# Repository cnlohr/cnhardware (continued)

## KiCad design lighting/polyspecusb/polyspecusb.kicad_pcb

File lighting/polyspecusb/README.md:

TODO:
1. Add resistor on ABC boards
2. Make D board (when more LEDs come)
3. Digitize the post-it notes.
4. Take pictures of the boards.
5. Classify radiance.
6. Fix flakeyness with 570funprog programmer

# Methodology

Test program:
```c
	SystemInit();
	Delay_Ms( 1800 );
	funGpioInitAll(); // Enable GPIOs
	GPIOC->CFGLR = 0x11111111;
	GPIOD->CFGLR = 0x44441144; // PD2..3 outputs
	while(1)
	{
		GPIOC->OUTDR = LEDMASK;
		GPIOD->OUTDR = (LEDMASK>>8)<<2;
		ADD_N_NOPS( 15 );
		GPIOC->OUTDR = 0x00;
		GPIOD->OUTDR = 0b0000;
		ADD_N_NOPS( 30 );  (or 300 for IR, etc.)
	}
```

Target wattage: ~1W (+/- 50%)

Settings on SpectraScan PR670:
ND1000 Filter, using 75mm 1:2.7
6ms integration time.
Focus on board

**Radiance values are approximate, and will vary by power, DO NOT USE FOR ABSOLUTE TERMS**

# LEDs

### 490-500 Ice Blue
Board A, top1, .66W (4.94V, 0.133A)
490-500, 3W Aixinde, "Ice Blue", 3W3535H490IB

### 450-460 Royal Blue
Board A, top2, .73W (4.94V, 0.149A)
450-460, 3W Aixinde, "Royal Blue", 3W3535XSJ450RB

### 520-530 Green
Board A, top3, .579W (4.95V, 0.116A)
520-530, 3W Aixinde, "Green" 3W3535XSJ520G / 3W3535XSJ5205?
1.57 W/sr/m^2, 516nm

### IR730
Board A, top4, LOW POWER, 2.27W (4.8V, 0.475A)
730nm, 3W Aixinde, "IR730" 3W3535Y730IR
3 W/sr/m^2, 730nm

### Deep Red 660
Board A, mid3, 1.341W (4.895V, 0.273A)
Unknown source (First batch)
7.55 W/sr/m^2, 662nm

### "Blue"
Board A, bottom3, 0.902W (4.931V, 0.182A)
Unknown source (very first batch)
4.18 W/sr/m^2, 462nm

### "Yellow"
Board A, mid2, 2.162W (4.829V, 0.447A)
YinYao Yellow 590-592 "3535XPE"
1.55 W/sr/m^2, 602nm

### 560-565 Green
Board A, bottom2, 1.211W (4.908V, .250A)
HF3534D120-3W-560-0745J9 560-565
1.2 W/sr/m^2, 552nm

### "Blue"
Board A, bottom1, .761W (4.946V, .152A)
3W3535BH470B (or is it 3W3535GH470B?) Blue Axinide 470-475
4.4 W/sr/m^2, 468nm

### "Golden"
Board A, mid1, LOW POWER 1.579W (4.879V, .372A)
3535XPE Yin Yao 1900k 3.0-3.2V Golden
1.56W/sr/m^2, SPREAD 622nm

## Board B

### 590-595 Yellow
Board B, top1, 1.38W (4.893V, 0.282A)
3W3535GH590Y
1.19W/sr/m^2 596nm

### "Red" 
Board B, top2, 1.72W (4.865V, 0.353A)
Unknown Red
8.72W/sr/m^2 634nm

### "Yellow"
Board B, top3, 1.40W (4.88V, 0.286A)
Yellow
1.47W/sr/m^2 598nm

### 590-595 Yellow 
Board B, top4, 1.37W (4.89V, .283A)
3W3535GH590Y Yellow 590-595nm Aixinde
1.33W/sr/m^2 596nm

### UV395
Board B, mid3, .722W (4.95V, .144A)
First Batch
3.46W/sr/m^2 398nm

### "440-445"
Board b, bottom3, .810W (4.94V, .161A)
First Batch
2.52 438

### "Golden"
Board B, mid2, LOW POWER 1.55W (4.875V, .312A)
First Batch
1.73 SPREAD 604

## "500-510"
Board b bottom2, 1.241W (4.91V, .258A)
First batch
3.2 498nm

## "460-470"
Board b, bottom1, .688W (4.95V, .140A)
First Batch
3.4 462nm

## 440-445 "Royal Blue"
Board b, mid1, .588W (4.95V, .136A)
First BAtch
3.86 438nm

## Blue "450-460"
Board c, top1, .709w (4.93V .147A)
2.62 W/sr/m^2 446nm

## Lake Blue "470-475"
Board c, top2, .617w (4.94V, .125A)
4.05 W/sr/m^2 468nm

## Ice Blue 490-495
Board c, top 3, .632W (4.94V, .127A)
2.5 W, 490nm

## 520-525
Board C, top 4, .574W (4.95V, .117A)
2.4 W, 514nm

## 545-550
Board C, mid 3, .658W (4.95V, .135A)
1.1W, 540nm

## 560-565
Board C, bottom3, LOW POWER, .8W (4.94V, .170A)
.617, 542nm

## 520-530
Board c, mid2, 1.004W (.493V, .260A)
3.92, 516nm

## 555-560
Board C, bottom2, 1.272W (4.897V, .266A)
2.31, 544nm

## 550-555
Board C, Bottom1, .707W (4.947V, .144A)
1.3, 544nm

## 530-535
Board C, mid1, .677 (4.949, .137A)
1.96, 526nm

## 560-570
D, top1  .678w (4.949V, .138A)
9.17, 552nm

## 580-585
D, top2 .648 (4.954V, .131A)
"Alt new order"
2.37, 612nm

## 575 "Cyan Yellow"
D, top3, .707 (4.95, .140A)
.923, 552nm

## 580-585 ZQQMU
D, top4, 1.203 (4.911, .241A)
.42, 584nm

##590-595
D, mid3, 1.291 (4.906, .253)
2.03, 598nm

##Red 620
D, bottom3, LOW POWER 1.71W (4.855, .367)
New Batch Red
3.93, 628nm

##585-590
D, middle2, 1.715 (4.856, .354A)
From group of oranges
1.38, 596nm

##620-630
D, bottom2, 2.52 (4.802, .521A)
Unknown but first group, probably oranges.
11.5W, 634nm

##600-605
D, bottom1, 1.908W (4.851V, .392A)
From first group of oranges
3.75, 616nm

##570-580
D, mid1, 1.11W (4.922, .229A)
I think yellows or oranges.
1.22, 558nm

## 660 deep red
E, top1, 1.178W (4.914, .239A)
8.17, 656nm

## 700nm 
E, top2, 1.756W (4.870, .359A)
Single Item (New)
9.31, 704nm

## 480-485
E, top3, .722W (4.951, .145A)
FROM NEW BATCH!
3.57, 484nm

## 940nm
E, top4, 3.11W (4.755, .653)
From new batch, single item
Deep glow. Does not effectively measure.

## 365-370
E, mid3, .811W (4.948, .167)
From new batch (I think, maybe?)
Cannot measure, has pale indigo glow.

## 850nm
E mid2, 3.46W (4.725, .731A)
No ND1000 filter, 100W/sr/m^2, off chart 780nm

## ??? Found on floor
E, bottom2, 1.08W (4.964, .223A)
3.8W, 514nm

## 1050nm
E bottom1, LOW POWER 3.064W (4.746, .647) (was 9W at low power)
What is this monstrosity?
I liked it because even while it's burning my corneas off, it has this really deep ethereal red glow.

## IR730
E mid1, LOW POWER 2.523W (4.800, .527)
3.52, 734nm

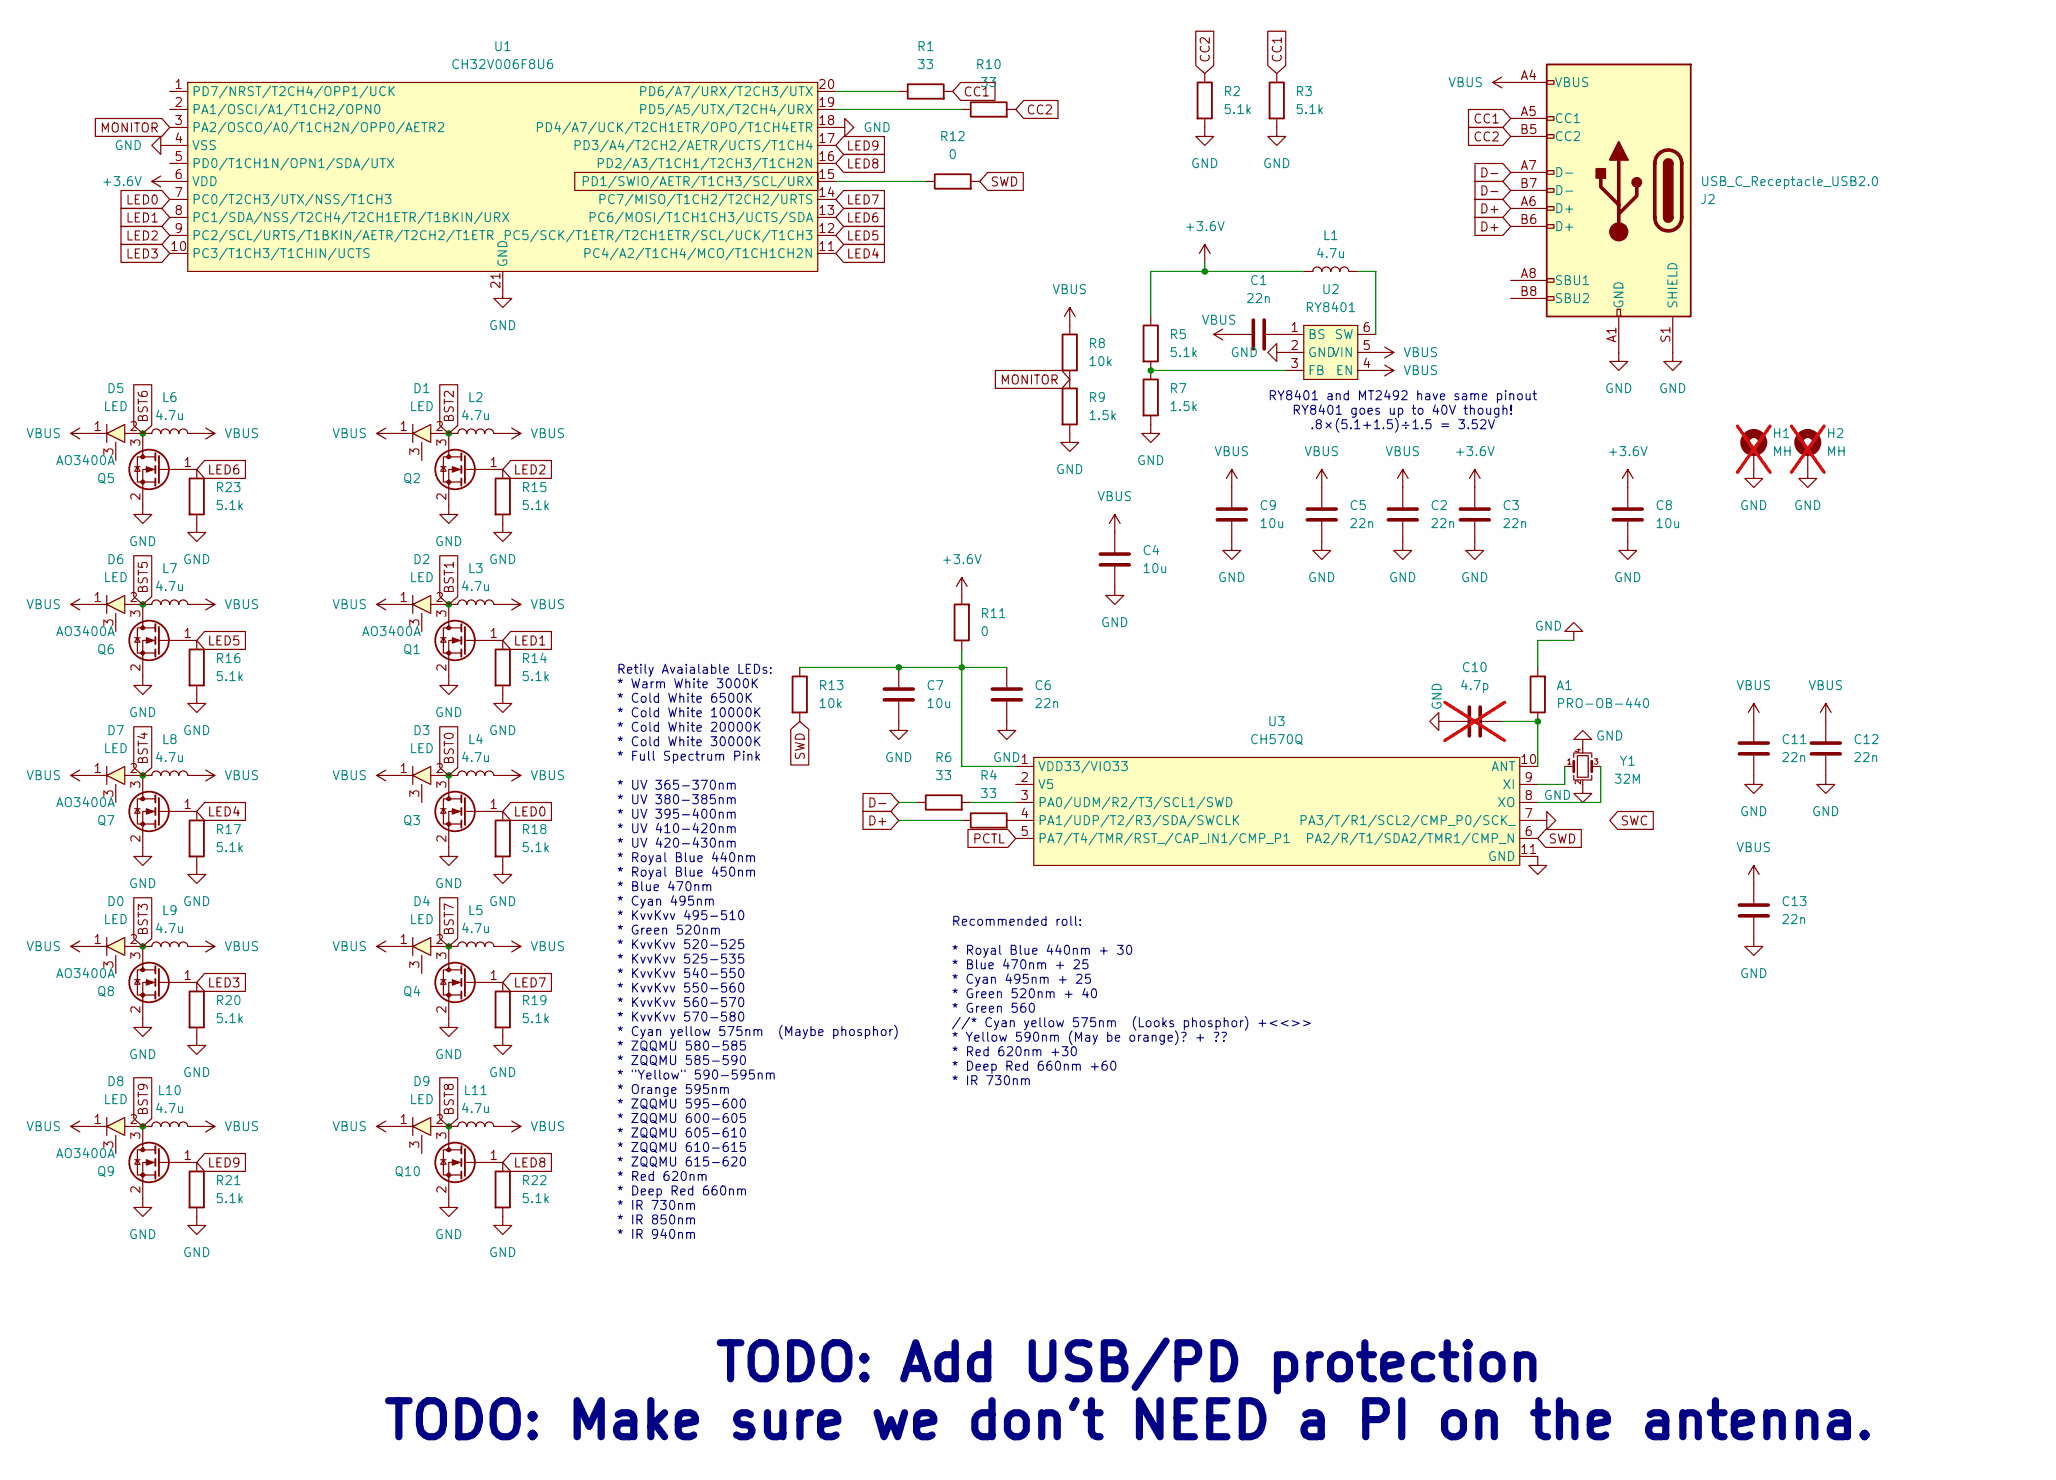
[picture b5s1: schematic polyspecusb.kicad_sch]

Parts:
A1: PRO-OB-440; Abracon_PRO-OB-440; LCSC C5122736
C1, C2, C3, C5, C6, C11, C12, C13: 22n; C_0402_1005Metric; LCSC C1532
C4, C7, C8, C9: 10u; C_0805_2012Metric; LCSC C15850
C10: 4.7p; C_0402_1005Metric; not fitted
D0, D1, D2, D3, D4, D5, D6, D7, D8, D9: LED; LED_3535_3W_W_PAD
H1, H2: MH; MountingHole_3.2mm_M3_ISO7380_Pad; not fitted
J2: USB_C_Receptacle_USB2.0; USB_C_SMT_ONLY_Receptacle_USB2.0; LCSC C2927040
L1, L2, L3, L4, L5, L6, L7, L8, L9, L10, L11: 4.7u; L_1008_2520Metric; LCSC C88528
Q1, Q2, Q3, Q4, Q5, Q6, Q7, Q8, Q9, Q10: AO3400A; SOT-23-EXTRASPACE; LCSC C20917
R1, R4, R6, R10: 33; R_0603_1608Metric; LCSC C23140
R2, R3, R5, R14, R15, R16, R17, R18, R19, R20, R21, R22, R23: 5.1k; R_0402_1005Metric; LCSC C25905
R7, R9: 1.5k; R_0402_1005Metric; LCSC C25867
R8, R13: 10k; R_0603_1608Metric; LCSC C25804
R11, R12: 0; R_0805_2012Metric; LCSC C17477
U1: CH32V006F8U6; QFN-20-1EP_3x3mm_P0.4mm_EP1.65x1.65mm; LCSC C42431288
U2: RY8401; SOT-23-6; LCSC C2912960
U3: CH570Q; DFN-10-1EP_3x3mm_P0.5mm_EP1.7x2.5mm; LCSC C49260680
Y1: 32M; Crystal_SMD_2016-4Pin_2.0x1.6mm; LCSC C718072

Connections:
+3.6V: C3.2, C8.2, L1.1, R5.1, R11.2, U1.6 (VDD)
BST0: D3.2, L4.1, Q3.3 (D)
BST1: D2.2, L3.1, Q1.3 (D)
BST2: D1.2, L2.1, Q2.3 (D)
BST3: D0.2, L9.1, Q8.3 (D)
BST4: D7.2, L8.1, Q7.3 (D)
BST5: D6.2, L7.1, Q6.3 (D)
BST6: D5.2, L6.1, Q5.3 (D)
BST7: D4.2, L5.1, Q4.3 (D)
BST8: D9.2, L11.1, Q10.3 (D)
BST9: D8.2, L10.1, Q9.3 (D)
CC1: J2.A5 (CC1), R1.2, R3.1
CC2: J2.B5 (CC2), R2.1, R10.2
D+: J2.A6 (D+), J2.B6 (D+), R4.1
D-: J2.A7 (D-), J2.B7 (D-), R6.1
GND: A1.2, C2.1, C3.1, C4.1, C5.1, C6.1, C7.1, C8.1, C9.1, C10.2, C11.1, C12.1, C13.1, H1.1, H2.1, J2.A1 (GND), J2.A12 (GND), J2.B1 (GND), J2.B12 (GND), J2.S1 (SHIELD), Q1.2 (S), Q2.2 (S), Q3.2 (S), Q4.2 (S), Q5.2 (S), Q6.2 (S), Q7.2 (S), Q8.2 (S), Q9.2 (S), Q10.2 (S), R2.2, R3.2, R7.2, R9.2, R14.2, R15.2, R16.2, R17.2, R18.2, R19.2, R20.2, R21.2, R22.2, R23.2, U1.4 (VSS), U1.18 (PD4/A7/UCK/T2CH1ETR/OPO/T1CH4ETR), U1.21 (GND), U2.2 (GND), U3.7 (PA3/T/R1/SCL2/CMP_P0/SCK_), U3.11 (GND), Y1.2, Y1.4
LED0: Q3.1 (G), R18.1, U1.7 (PC0/T2CH3/UTX/NSS/T1CH3)
LED1: Q1.1 (G), R14.1, U1.8 (PC1/SDA/NSS/T2CH4/T2CH1ETR/T1BKIN/URX)
LED2: Q2.1 (G), R15.1, U1.9 (PC2/SCL/URTS/T1BKIN/AETR/T2CH2/T1ETR)
LED3: Q8.1 (G), R20.1, U1.10 (PC3/T1CH3/T1CHIN/UCTS)
LED4: Q7.1 (G), R17.1, U1.11 (PC4/A2/T1CH4/MCO/T1CH1CH2N)
LED5: Q6.1 (G), R16.1, U1.12 (PC5/SCK/T1ETR/T2CH1ETR/SCL/UCK/T1CH3)
LED6: Q5.1 (G), R23.1, U1.13 (PC6/MOSI/T1CH1CH3/UCTS/SDA)
LED7: Q4.1 (G), R19.1, U1.14 (PC7/MISO/T1CH2/T2CH2/URTS)
LED8: Q10.1 (G), R22.1, U1.16 (PD2/A3/T1CH1/T2CH3/T1CH2N)
LED9: Q9.1 (G), R21.1, U1.17 (PD3/A4/T2CH2/AETR/UCTS/T1CH4)
MONITOR: R8.2, R9.1, U1.3 (PA2/OSCO/A0/T1CH2N/OPP0/AETR2)
unnamed: R12.1, U1.15 (PD1/SWIO/AETR/T1CH3/SCL/URX)
unnamed: R10.1, U1.19 (PD5/A5/UTX/T2CH4/URX)
unnamed: R1.1, U1.20 (PD6/A7/URX/T2CH3/UTX)
unnamed: C1.2, U2.1 (BS)
unnamed: R5.2, R7.1, U2.3 (FB)
unnamed: L1.2, U2.6 (SW)
unnamed: A1.1, C10.1, U3.10 (ANT)
unnamed: R6.2, U3.3 (PA0/UDM/R2/T3/SCL1/SWD)
unnamed: R4.2, U3.4 (PA1/UDP/T2/R3/SDA/SWCLK)
unnamed: C6.2, C7.2, R11.1, R13.1, U3.1 (VDD33/VIO33)
unnamed: U3.9 (XI), Y1.1
unnamed: U3.8 (XO), Y1.3
PCTL: U3.5 (PA7/T4/TMR/RST_/CAP_IN1/CMP_P1)
SWD: R12.2, R13.2, U3.6 (PA2/R/T1/SDA2/TMR1/CMP_N)
VBUS: C1.1, C2.2, C4.2, C5.2, C9.2, C11.2, C12.2, C13.2, D0.1, D1.1, D2.1, D3.1, D4.1, D5.1, D6.1, D7.1, D8.1, D9.1, J2.A4 (VBUS), J2.A9 (VBUS), J2.B4 (VBUS), J2.B9 (VBUS), L2.2, L3.2, L4.2, L5.2, L6.2, L7.2, L8.2, L9.2, L10.2, L11.2, R8.1, U2.4 (EN), U2.5 (VIN)

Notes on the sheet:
Retily Avaialable LEDs: * Warm White 3000K * Cold White 6500K * Cold White 10000K * Cold White 20000K * Cold White 30000K * Full Spectrum Pink * UV 365-370nm * UV 380-385nm * UV 395-400nm * UV 410-420nm * UV 420-430nm * Royal Blue 440nm * Royal Blue 450nm * Blue 470nm * Cyan 495nm * KvvKvv 495-510 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
Recommended roll: * Royal Blue 440nm + 30 * Blue 470nm + 25 * Cyan 495nm + 25 * Green 520nm + 40 * Green 560 //* Cyan yellow 575nm (Looks phosphor) +<<>> * Yellow 590nm (May be orange)? + ?? * Red 620nm +30 * Deep Red 660nm +60 * IR 730nm
TODO: Add USB/PD protection TODO: Make sure we don't NEED a PI on the antenna.
RY8401 and MT2492 have same pinout RY8401 goes up to 40V though! .8×(5.1+1.5)÷1.5 = 3.52V

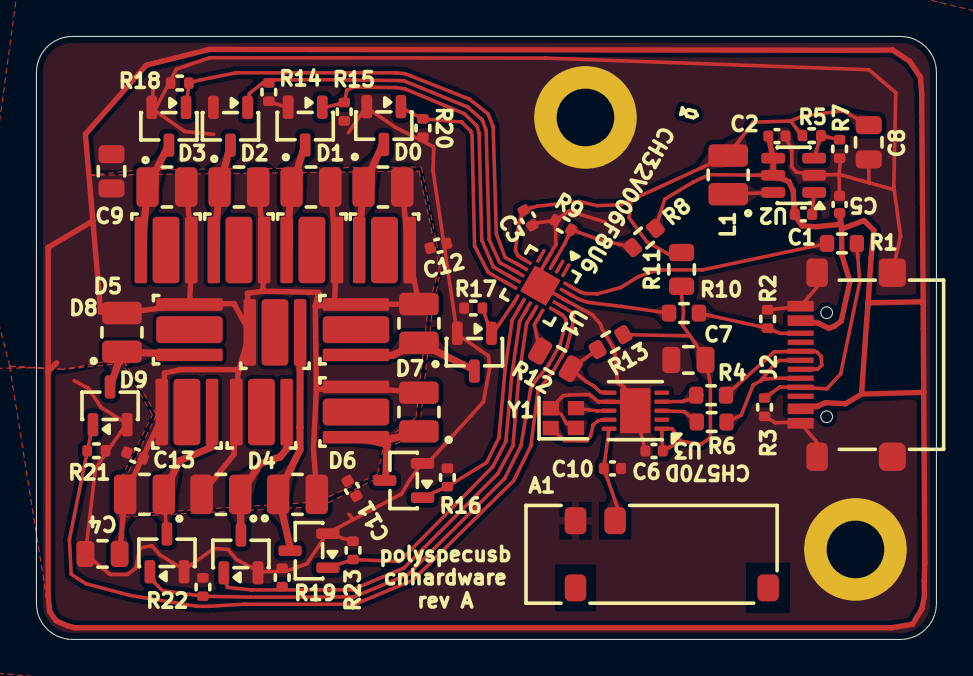
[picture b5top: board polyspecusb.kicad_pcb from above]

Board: 2 copper layers, 50.0 x 33.5 mm, 75 parts (0 on the bottom side), 41 nets.
